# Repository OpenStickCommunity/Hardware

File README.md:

# Open Stick Community hardware repo

This repository is a collection of open-source hardware designs which have been submitted to the project.

# Designs

3D Prints

- [3D Printable Stand - Small](/3D%20Prints/3D%20Printable%20Stand/README.md) - Designed by TheTrain
- [3D Printable Stand - Large](/3D%20Prints/3D%20Printable%20Stand/README.md) - Designed by TheTrain
- [3D Printable Fightstick Case](/3D%20Prints/Fightstick%20Case/README.md) - Designed by TheTrain
- [3D Printable Open Stick Mini](/3D%20Prints/Open%20Stick%20Mini/README.md) - Designed by TheTrain
- [3D Printable Fightstick Case XL](/3D%20Prints/Fightstick%20Case/Community%20submissions/3D%20print%20files/Fightstick%20XL/Open%20Stick%20XL%20-%20Main%20Frame%20(x4%20Buttons).stl) - Designed by Lucipher
- [3D Printable Open Stick Modular](/3D%20Prints/Open%20Stick%20Modular%20(OSM)/README.md) - Designed by TheTrain
- [3D Printable Open Stick Modular - Mini](/3D%20Prints/Open%20Stick%20Modular%20-%20Mini%20(OSM-Mini)/README.md) - Designed by TheTrain
- [3D Printable Open Stick Modular - Slim](/3D%20Prints/Open%20Stick%20Modular%20-%20Slim%20(OSM-Slim)/README.md) - Designed by TheTrain
- [3D Printable Open Stick Astro](/3D%20Prints/Open%20Stick%20Astro%20(OSASTRO)/README.md) - Designed by TheTrain
- [3D Printable OSBMX v2 Buttons](/3D%20Prints/OSBMX%20v2/README.md) - Designed by TheTrain
- [3D Printable OSBLP v2 Buttons](/3D%20Prints/OSBLP%20v2/README.md) - Designed by TheTrain
- [3D Printable OSBMX v2 SiTong Edition Buttons](/3D%20Prints/OSBMX%20v2/Community%20submissions/OSBMX%20v2%20-%20SiTong%20Edition/README.md) - Designed by TheTrain (remixed from the OSBLP v2 by TheTrain)
- [3D Printable OSBLP v2 SiTong Edition Buttons](/3D%20Prints/OSBLP%20v2/Community%20submissions/OSBLP%20v2%20-%20SiTong%20Edition/README.md) - Designed by TheTrain (remixed from the OSBLP v2 by TheTrain)
- [3D Printable OSBHE v2 Buttons](/3D%20Prints/OSBHE%20v2/README.md) - Designed by TheTrain
- [3D Printable OSB Plug](/3D%20Prints/OSB%20Plug/README.md) - Designed by TheTrain
- [3D Printable OSB Analog Stick](/3D%20Prints/OSB%20Analog%20Stick/README.md) - Designed by TheTrain
- [Open Source Arcade Stand - OSAS](/3D%20Prints/Open%20Source%20Arcade%20Stand%20(OSAS)/README.md) - Designed by TheTrain

GP2040-CE Official Boards

- [RP2040 Advanced Breakout Board v5.6E with USB Passthrough](/Boards/GP2040-CE%20Official%20Boards/RP2040%20Advanced%20Breakout%20Board/RP2040%20Advanced%20Breakout%20Board%20-%20Passthrough/README.md) - Designed by TheTrain
- [RP2040 Advanced Breakout Board v5.2E (no USB Passthrough)](/Boards/GP2040-CE%20Official%20Boards/RP2040%20Advanced%20Breakout%20Board/RP2040%20Advanced%20Breakout%20Board/README.md) - Designed by TheTrain
- [RP2040 Basic Breakout Board v5.4E with USB Passthrough](/Boards/GP2040-CE%20Official%20Boards/RP2040%20Basic%20Breakout%20Board/RP2040%20Basic%20Breakout%20Board%20-%20Passthrough/README.md) - Designed by TheTrain
- [RP2040 Basic Breakout Board v5.4E (no USB Passthrough)](/Boards/GP2040-CE%20Official%20Boards/RP2040%20Basic%20Breakout%20Board/RP2040%20Basic%20Breakout%20Board/README.md) - Designed by TheTrain
- [RP2040 Mini Breakout Board v7.5E with USB Passthrough](/Boards/GP2040-CE%20Official%20Boards/RP2040%20Mini%20Breakout%20Board/RP2040%20Mini%20Breakout%20Board%20-%20Passthrough/README.md) - Designed by TheTrain
- [RP2040 Mini Breakout Board v7.3E (no USB Passthrough)](/Boards/GP2040-CE%20Official%20Boards/RP2040%20Mini%20Breakout%20Board/RP2040%20Mini%20Breakout%20Board/README.md) - Designed by TheTrain
- [RP2040 Quick Solder Breakout Board v1.0 (no USB Passthrough)](/Boards/GP2040-CE%20Official%20Boards/RP2040%20Quick%20Solder%20Breakout%20Board/README.md) - Designed by TheTrain

GP2040-CE Official Controllers

- [ARC Accessibility Controller](/Boards/GP2040-CE%20Official%20Controllers/ARC%20Accessibility%20Controller/README.md) - Designed by TheTrain
- [Flatbox Rev 5 RGB](/Boards/GP2040-CE%20Official%20Controllers/Flatbox%20Rev%205%20RGB/README.md) - Remixed by TheTrain from the Flatbox Rev 5 by Jfedor
- [Flatbox Rev 5 Passthrough](/Boards/GP2040-CE%20Official%20Controllers/Flatbox%20Rev%205%20Passthrough/README.md) - Remixed by TheTrain from the Flatbox Rev 5 by Jfedor
- [Open_Core0 v2.0](/Boards/GP2040-CE%20Official%20Controllers/Open_Core0/README.md) - Designed by TheTrain
- [Open_Core0 WASD v2.0](/Boards/GP2040-CE%20Official%20Controllers/Open_Core0%20WASD/README.md) - Designed by TheTrain
- [Open_Core0 MIXUP](/Boards/GP2040-CE%20Official%20Controllers/Open_Core0%20MIXUP/README.md) - Designed by TheTrain
- [Zero_Rhythm v1.0](/Boards/GP2040-CE%20Official%20Controllers/Zero%20Rhythm/README.md) - Designed by TheTrain
- [Pocket Pad](/Boards/GP2040-CE%20Official%20Controllers/Pocket%20Pad/README.md) - Designed by TheTrain
- [Pocket Pad WASD](/Boards/GP2040-CE%20Official%20Controllers/Pocket%20Pad%20WASD/README.md) - Designed by TheTrain
- [Mini Pad](/Boards/GP2040-CE%20Official%20Controllers/Mini%20Pad/README.md) - Designed by TheTrain

Retail Stick Replacement Boards

- [Hori Fighting Edge PS3 (FE PS3)](/Boards/Retail%20Stick%20Replacement%20Boards/Hori%20Fighting%20Edge%20PS3%20(FE%20PS3)/README.md) - Designed by TheTrain
- [Hori Fighting Edge PS4 (FE PS4)](/Boards/Retail%20Stick%20Replacement%20Boards/Hori%20Fighting%20Edge%20PS4%20(FE%20PS4)/README.md) - Designed by TheTrain
- [Hori Real Arcade Pro N PS4 (RAP N PS4)](/Boards/Retail%20Stick%20Replacement%20Boards/Hori%20Real%20Arcade%20Pro%20N%20PS4%20(RAP%20N%20PS4)/README.md) - Designed by TheTrain
- [Hori Real Arcade Pro VLX PS3 (RAP VLX PS3)](/Boards/Retail%20Stick%20Replacement%20Boards/Hori%20Real%20Arcade%20Pro%20VLX%20PS3%20(RAP%20VLX%20PS3)/README.md) - Designed by TheTrain
- [SEGA Dreamcast Twin Stick (with USB Passthrough)](/Boards/Retail%20Stick%20Replacement%20Boards/SEGA%20Dreamcast%20Twin%20Stick%20(with%20USB%20Passthrough)/README.md) - Designed by indigotrance

Supported Boards

- [Ghost Auth v2.0](/Boards/Supported%20Boards/Ghost%20Auth/README.md) - Designed by TheTrain
- [GP2040 Keyboard converter](/Boards/Supported%20Boards/GP2040%20Keyboard%20Converter/Waveshare%20Zero-PCB/README.md) - Designed by Infraredaces
- [USB Pasthrough Add-on Board](/Boards/Supported%20Boards/USB%20Passthrough%20Board/README.md) - Designed by TheTrain
- [Tiny USB Hub v1.2 - 2x USB with USB C](/Boards/Supported%20Boards/USB%20Hubs/Tiny%20USB%20Hub%20v1.2e/README.md) - Designed by TheTrain
- [Tiny USB Hub v1.3 - 2x USB Direct Connect](/Boards/Supported%20Boards/USB%20Hubs/Tiny%20USB%20Hub%20v1.3e/README.md) - Designed by TheTrain
- [Tiny USB Hub v1.3 v2 - 2x USB Direct Connect](/Boards/Supported%20Boards/USB%20Hubs/Tiny%20USB%20Hub%20v1.3e%20v2/README.md) - Designed by TheTrain
- [Tiny USB Hub v1.4 - 4x USB Direct Connect](/Boards/Supported%20Boards/USB%20Hubs/Tiny%20USB%20Hub%20v1.4e/README.md) - Designed by TheTrain
- [HE Breakout Board v1.1](/Boards/Supported%20Boards/HE%20Breakout%20Board/README.md) - Designed by TheTrain
- [RPBoy v1.0](/Boards/Supported%20Boards/RPBoy/README.md) - Designed by TheTrain
- [RPBoy Mini v2.0](/Boards/Supported%20Boards/RPBoy%20Mini/README.md) - Designed by TheTrain

Miscellaneous

- [Haute42/COSMOX Bottom Foam](/Miscellaneous/Haute42%20COSMOX%20Bottom%20Foam/README.md) - Designed by TheTrain
- [Sanjuks V3 AM5 Adapter Plate](/Miscellaneous/Sanjuks%20V3%20AM5%20Adapter%20Plate/README.md) - Designed by TheTrain
- [Sanjuks Style Nobi Topper](/Miscellaneous/Sanjuks%20Style%20Nobi%20Topper/README.md) - Designed by TheTrain
- [Open LED Project - Sanwa 30mm RGB LEDs](/Miscellaneous/Open%20LED%20Project%20-%20Sanwa%2030mm%20RGB%20LED/README.md) - Designed by TheTrain
- [Open LED Project - Addressable RGB LED Light Bar](/Miscellaneous/Open%20LED%20Project%20-%20Addressable%20RGB%20LED%20Light%20Bar/README.md) - Designed by TheTrain
- [Nintendo Switch Art Cart](/Miscellaneous/Nintendo%20Switch%20Art%20Carts/README.md) - Designed by TheTrain, art template by TheTrain
- [Sanwa JLF Plate Cover](/Miscellaneous/Sanwa%20JLF%20Plate%20Cover/README.md) - Designed by TheTrain

Trains Vewlix Stuff

- [Vewlix Coin Return Adapter](/Trains%20Vewlix%20Stuff/Vewlix%20Coin%20Return%20Adapter/README.md) - Designed by TheTrain
- [Vewlix Coin Return Slot](/Trains%20Vewlix%20Stuff/Vewlix%20Coin%20Return%20Slot/README.md) - Designed by TheTrain
- [Vewlix Coin Mech](/Trains%20Vewlix%20Stuff/Vewlix%20Coin%20Mech/README.md) - Designed by TheTrain
- [Vewlix Stickers](/Trains%20Vewlix%20Stuff/Vewlix%20Stickers/README.md) - Remixes and customs by TheTrain
- [Vewlix Control Panel SiTong Adapter Rings](/Trains%20Vewlix%20Stuff/Vewlix%20Control%20Panel%20SiTong%20Adapter%20Rings/README.md) - Designed by TheTrain
- [Vewlix NESiCA NFC Reader](/Trains%20Vewlix%20Stuff/Vewlix%20NESiCA%20NFC%20Reader/README.md) - Designed by TheTrain
- [Vewlix Sub-Panel Art and Cut Files](/Trains%20Vewlix%20Stuff/Vewlix%20Sub-Panel%20Art%20and%20Cut%20Files/README.md) - Designed by Jermaine Davis

Trains Sim Racing Stuff

- [Logitech G PRO RS Wheel Hub wall mount](/Trains%20Sim%20Racing%20Stuff/Logitech%20G%20PRO%20RS%20Wheel%20Hub%20wall%20mount/README.md) - Designed by TheTrain
- [Logitech G PRO RS Wheel Hub 4040 mount](/Trains%20Sim%20Racing%20Stuff/Logitech%20G%20PRO%20RS%20Wheel%20Hub%204040%20mount/README.md) - Designed by TheTrain
- [Logitech G PRO RS Wheel Hub Shifter Pad Mod](/Trains%20Sim%20Racing%20Stuff/Logitech%20RS%20Wheel%20Hub%20Shifter%20Pad%20Mod/README.md) - Designed by TheTrain
- [Logitech G PRO RS Wheel Rim template](/Trains%20Sim%20Racing%20Stuff/Logitech%20G%20PRO%20RS%20Wheel%20Rim%20template/README.md) - Designed by TheTrain
- [Wind Sim](/Trains%20Sim%20Racing%20Stuff/Wind%20Sim/README.md) - Designed by TheTrain
- [LapTimer](/Trains%20Sim%20Racing%20Stuff/Laptimer/README.md) - Designed by TheTrain
- [Porsche GT3 R Plate](/Trains%20Sim%20Racing%20Stuff/Porsche%20911%20GT3%20R%20plate/README.md) - Designed by TheTrain

Trains Theatrhythm Stuff
- [Theatrhythm - All-Star Carnival Manual](/Trains%20Theatrhythm%20Stuff/Theatrhythm%20Manual/Theatrhythm%20-%20All-Star%20Carnival%20-%20Manual.pdf)
- [Theatrhythm - All-Star Carnival JLF Shaft](/Trains%20Theatrhythm%20Stuff/Theatrhythm%20JLF%20shaft/README.md) - Designed by LayerShift
- [Theatrhythm - All-Star Carnival Side Plexi Art](/Trains%20Theatrhythm%20Stuff/Theatrhythm%20ASC%20Arcade%20Cabinet%20Art/Theatrhythm%20ASC%20Side%20Plexi%20Art/README.md) - Designed by TheTrain
- [Theatrhythm - All-Star Carnival Front Control Panel Art](/Trains%20Theatrhythm%20Stuff/Theatrhythm%20ASC%20Arcade%20Cabinet%20Art/Theatrhythm%20ASC%20Front%20Control%20Panel%20Art/README.md) - Designed by TheTrain
- [Theatrhythm - All-Star Carnival NESiCA Reader Art](/Trains%20Theatrhythm%20Stuff/Theatrhythm%20ASC%20Arcade%20Cabinet%20Art/Theatrhythm%20ASC%20NESiCA%20Reader%20Art/README.md) - Designed by TheTrain
- [Theatrhythm - All-Star Carnival Coin Sticker Art](/Trains%20Theatrhythm%20Stuff/Theatrhythm%20ASC%20Arcade%20Cabinet%20Art/Theatrhythm%20ASC%20Coin%20Sticker%20Art/README.md) - Designed by TheTrain

Trains Arcade Machine Manual Stuff

- [Taito Vewlix L - Manual - Part 1](/Trains%20Vewlix%20Stuff/Vewlix%20Manual/Taito%20Vewlix%20L%20-%20Manual%20-%20Part%201.pdf)
- [Taito Vewlix L - Manual - Part 2](/Trains%20Vewlix%20Stuff/Vewlix%20Manual/Taito%20Vewlix%20L%20-%20Manual%20-%20Part%202.pdf)
- [Taito Vewlix L - Manual - Part 3](/Trains%20Vewlix%20Stuff/Vewlix%20Manual/Taito%20Vewlix%20L%20-%20Manual%20-%20Part%203.pdf)
- [Theatrhythm - All-Star Carnival](/Trains%20Theatrhythm%20Stuff/Theatrhythm%20Manual/Theatrhythm%20-%20All-Star%20Carnival%20-%20Manual.pdf)

Tutorials

- [Focus Attack RGB LED Board Configuration](/Tutorials/Focus%20Attack%20LED%20Board%20Configuration/README.md) for the [RP2040 Advanced Breakout Board v5.6](/Boards/GP2040-CE%20Official%20Boards/RP2040%20Advanced%20Breakout%20Board/RP2040%20Advanced%20Breakout%20Board%20-%20Passthrough/README.md) - Written by TheTrain
- [USB Passthrough Add-on Board Installation](/Tutorials/USB%20Passthrough%20Board%20Installation/README.md) - Written by TheTrain
- [Logitech RS Wheel Hub Shifter Pad Mod](/Tutorials/Logitech%20RS%20Wheel%20Hub%20Shifter%20Pad%20Mod/README.md) - Written by TheTrain

Vendor Resources

- [GP2040-CE Logo Files](/Vendor%20Resources/GP2040-CE%20Logo%20files/README.md)

# Contributing

Any design submitted to this repository must be submitted by the original copyright holder and include a [license](#licensing). If your license requires attribution, you must provide details on how to appropriately attribute the design.

# Copyright

All copyrights are retained by the original author(s) unless the copyright is explicitly transferred to the Open Stick Community.

# Licensing

Check the LICENSE of each design for details on how the design can be used.

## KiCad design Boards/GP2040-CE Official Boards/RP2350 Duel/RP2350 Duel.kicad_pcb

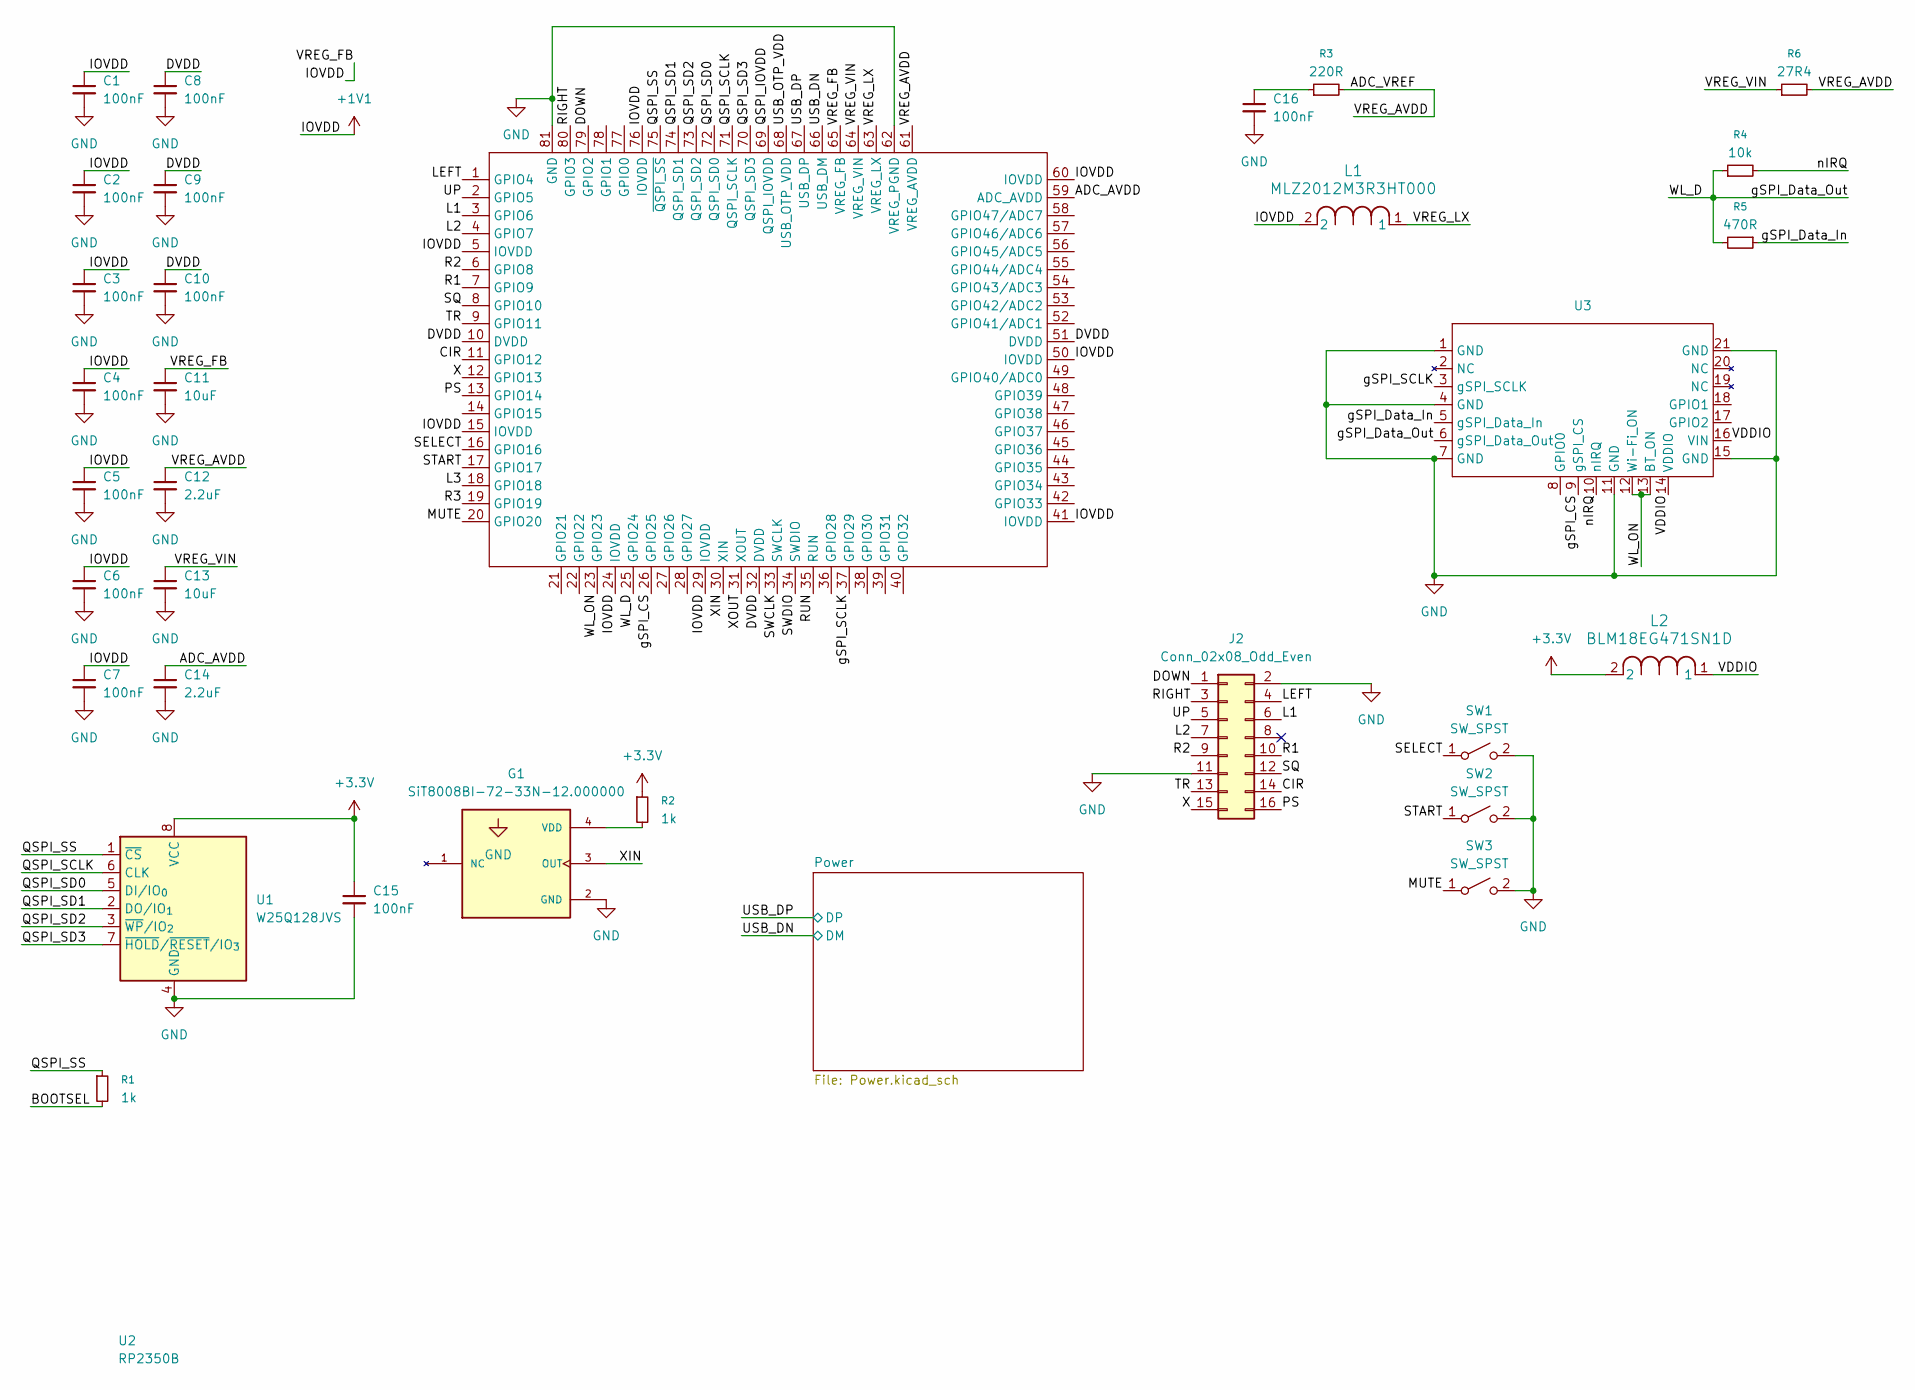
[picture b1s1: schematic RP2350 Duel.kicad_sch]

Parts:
C1, C2, C3, C4, C5, C6, C7, C8, C9, C10, C15, C16: 100nF; C_0603_1608Metric_Pad1.08x0.95mm_HandSolder
C11, C13: 10uF; C_0603_1608Metric_Pad1.08x0.95mm_HandSolder
C12, C14: 2.2uF; C_0603_1608Metric_Pad1.08x0.95mm_HandSolder
G1: SiT8008BI-72-33N-12.000000; OSC_SiT8008BI-72-33N-12.000000; PARTREV 1.08
J2: Conn_02x08_Odd_Even; FlexPCB
L1: MLZ2012M3R3HT000; IND_2012_TDK
L2: BLM18EG471SN1D; IND_BLM18_0603_MUR
R1, R2: 1k; R_0603_1608Metric_Pad0.98x0.95mm_HandSolder
R3: 220R; R_0603_1608Metric_Pad0.98x0.95mm_HandSolder
R4: 10k; R_0603_1608Metric_Pad0.98x0.95mm_HandSolder
R5: 470R; R_0603_1608Metric_Pad0.98x0.95mm_HandSolder
R6: 27R4; R_0603_1608Metric_Pad0.98x0.95mm_HandSolder
SW1, SW2, SW3: SW_SPST; SKRWAEE030
U1: W25Q128JVS; SOIC-8_5.3x5.3mm_P1.27mm
U2: RP2350B; QFN-80-1EP_10x10mm_P0.4mm_EP3.4x3.4mm
U3: RM2

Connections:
+1V1: C1.1, C2.1, C3.1, C4.1, C5.1, C6.1, C7.1, C11.1, L1.2, U2.5 (IOVDD), U2.15 (IOVDD), U2.24 (IOVDD), U2.29 (IOVDD), U2.41 (IOVDD), U2.50 (IOVDD), U2.60 (IOVDD), U2.65 (VREG_FB), U2.76 (IOVDD)
+3.3V: C15.1, L2.2, R2.1, U1.8 (VCC); also elsewhere on the board
/ADC_AVDD: C14.1, U2.59 (ADC_AVDD)
/ADC_VREF: C12.1, R3.2, R6.2, U2.61 (VREG_AVDD)
/BOOTSEL: R1.2
/CIR: J2.14, U2.11 (GPIO12)
/DOWN: J2.1, U2.79 (GPIO2)
/DVDD: C8.1, C9.1, C10.1, U2.10 (DVDD), U2.32 (DVDD), U2.51 (DVDD)
/L1: J2.6, U2.3 (GPIO6)
/L2: J2.7, U2.4 (GPIO7)
/L3: U2.18 (GPIO18)
/LEFT: J2.4, U2.1 (GPIO4)
/MUTE: SW3.1 (A), U2.20 (GPIO20)
/PS: J2.16, U2.13 (GPIO14)
/QSPI_IOVDD: U2.69 (QSPI_IOVDD)
/QSPI_SCLK: U1.6 (CLK), U2.71 (QSPI_SCLK)
/QSPI_SD0: U1.5 (DI/IO_{0}), U2.72 (QSPI_SD0)
/QSPI_SD1: U1.2 (DO/IO_{1}), U2.74 (QSPI_SD1)
/QSPI_SD2: U1.3 (~WP/IO_{2}), U2.73 (QSPI_SD2)
/QSPI_SD3: U1.7 (~HOLD/~RESET/IO_{3}), U2.70 (QSPI_SD3)
/QSPI_SS: R1.1, U1.1 (~CS), U2.75 (~QSPI_SS)
/R1: J2.10, U2.7 (GPIO9)
/R2: J2.9, U2.6 (GPIO8)
/R3: U2.19 (GPIO19)
/RIGHT: J2.3, U2.80 (GPIO3)
/RUN: U2.35 (RUN)
/SELECT: SW1.1 (A), U2.16 (GPIO16)
/SQ: J2.12, U2.8 (GPIO10)
/START: SW2.1 (A), U2.17 (GPIO17)
/SWCLK: U2.33 (SWCLK)
/SWDIO: U2.34 (SWDIO)
/TR: J2.13, U2.9 (GPIO11)
/UP: J2.5, U2.2 (GPIO5)
/USB_DN: U2.66 (USB_DM); also elsewhere on the board
/USB_DP: U2.67 (USB_DP); also elsewhere on the board
/USB_OTP_VDD: U2.68 (USB_OTP_VDD)
/VDDIO: L2.1, U3.14 (VDDIO), U3.16 (VIN)
/VREG_LX: L1.1, U2.63 (VREG_LX)
/VREG_VIN: C13.1, R6.1, U2.64 (VREG_VIN)
/WL_D: R4.1, R5.2, U2.25 (GPIO24), U3.6 (gSPI_Data_Out)
/WL_ON: U2.23 (GPIO23), U3.12 (Wi-Fi_ON), U3.13 (BT_ON)
/X: J2.15, U2.12 (GPIO13)
/XIN: G1.3 (OUT), U2.30 (XIN)
/XOUT: U2.31 (XOUT)
/gSPI_CS: U2.26 (GPIO25), U3.9 (gSPI_CS)
/gSPI_Data_In: R5.1, U3.5 (gSPI_Data_In)
/gSPI_SCLK: U2.37 (GPIO29), U3.3 (gSPI_SCLK)
/nIRQ: R4.2, U3.10 (nIRQ)
GND: C1.2, C2.2, C3.2, C4.2, C5.2, C6.2, C7.2, C8.2, C9.2, C10.2, C11.2, C12.2, C13.2, C14.2, C15.2, C16.2, G1.2 (GND), J2.2, J2.11, SW1.2 (B), SW2.2 (B), SW3.2 (B), U1.4 (GND), U2.62 (VREG_PGND), U2.81 (GND), U3.1 (GND), U3.4 (GND), U3.7 (GND), U3.11 (GND), U3.15 (GND), U3.21 (GND); also elsewhere on the board
unnamed: C16.1, R3.1
unnamed: G1.4 (VDD), R2.2

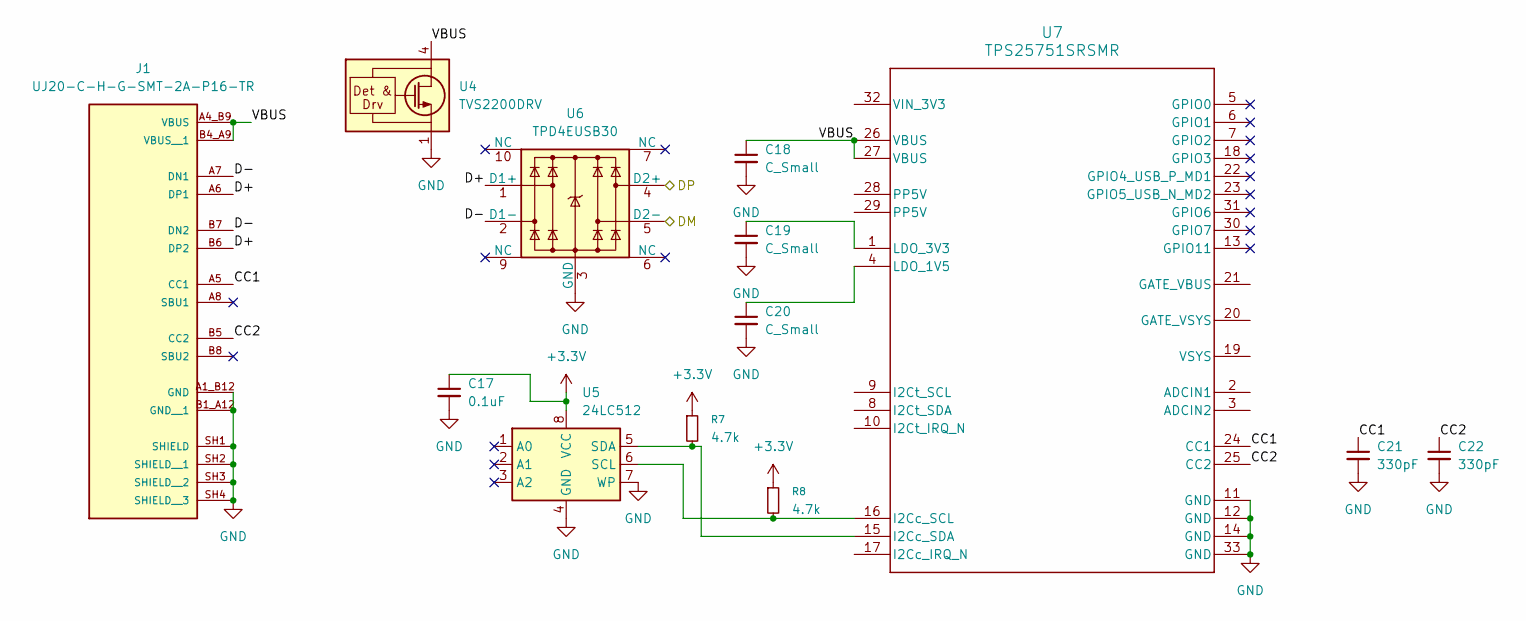
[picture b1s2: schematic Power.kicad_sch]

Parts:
C17: 0.1uF; C_0603_1608Metric_Pad1.08x0.95mm_HandSolder
C18, C19, C20: C_Small; C_0603_1608Metric_Pad1.08x0.95mm_HandSolder
C21, C22: 330pF; C_0603_1608Metric_Pad1.08x0.95mm_HandSolder
J1: UJ20-C-H-G-SMT-2A-P16-TR; SAMESKY_UJ20-C-H-G-SMT-2A-P16-TR; PARTREV 1.0
R7, R8: 4.7k; R_0603_1608Metric_Pad0.98x0.95mm_HandSolder
U4: TVS2200DRV; WSON-6-1EP_2x2mm_P0.65mm_EP1x1.6mm
U5: 24LC512
U6: TPD4EUSB30; USON-10_2.5x1.0mm_P0.5mm
U7: TPS25751SRSMR; RSM0032B-MFG

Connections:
+3.3V: C17.1, R7.1, R8.1, U5.8 (VCC); also elsewhere on the board
/Power/CC1: C21.1, J1.A5 (CC1), U7.24 (CC1)
/Power/CC2: C22.1, J1.B5 (CC2), U7.25 (CC2)
/Power/D+: J1.A6 (DP1), J1.B6 (DP2), U6.1 (D1+)
/Power/D-: J1.A7 (DN1), J1.B7 (DN2), U6.2 (D1-)
/Power/VBUS: C18.1, J1.A4_B9 (VBUS), J1.B4_A9 (VBUS__1), U4.4 (IN), U4.5 (IN), U4.6 (IN), U7.26 (VBUS), U7.27 (VBUS)
/USB_DN: U6.5 (D2-); also elsewhere on the board
/USB_DP: U6.4 (D2+); also elsewhere on the board
GND: C17.2, C18.2, C19.2, C20.2, C21.2, C22.2, J1.A1_B12 (GND), J1.B1_A12 (GND__1), J1.SH1 (SHIELD), J1.SH2 (SHIELD__1), J1.SH3 (SHIELD__2), J1.SH4 (SHIELD__3), U4.1 (GND), U4.2 (GND), U4.3 (GND), U4.7 (GND), U5.4 (GND), U5.7 (WP), U6.3 (GND), U6.8 (GND), U7.11 (GND), U7.12 (GND), U7.14 (GND), U7.33 (GND); also elsewhere on the board
unnamed: R8.2, U5.6 (SCL), U7.16 (I2Cc_SCL)
unnamed: R7.2, U5.5 (SDA), U7.15 (I2Cc_SDA)
unnamed: C20.1, U7.4 (LDO_1V5)
unnamed: C19.1, U7.1 (LDO_3V3)

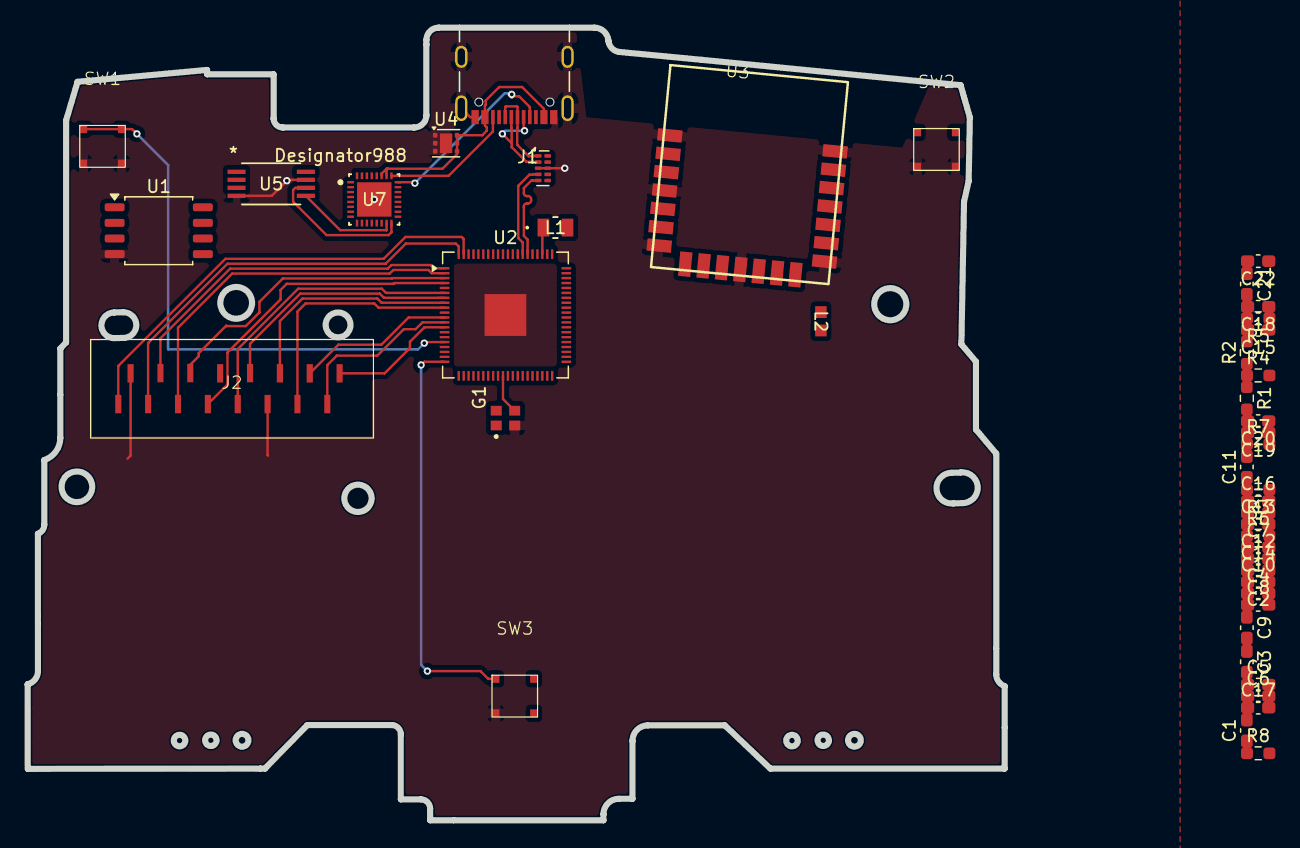
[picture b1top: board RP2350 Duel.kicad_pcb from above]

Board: 4 copper layers, 79.5 x 64.5 mm, 45 parts (0 on the bottom side), 51 nets.

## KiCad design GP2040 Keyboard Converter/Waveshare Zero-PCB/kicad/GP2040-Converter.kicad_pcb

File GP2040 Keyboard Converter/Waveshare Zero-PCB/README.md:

# GP2040-CE Keyboard Converter

---

***NOTE: Keyboard Host Configuration has not yet been implemented into the GP2040-CE project as part of the Main Release as of GP2040-CE v0.7.3***

## Attribution

The following text must be included in any distribution of derivitives of this board. All links must also be included.

Copyright 2023 [InfraredAces](https://github.com/InfraredAces)

[Licensed under CC BY 4.0](https://creativecommons.org/licenses/by/4.0/)

Changes from the original design:
  - list any changes you make here

## Summary

The GP2040-CE Keyboard Converter Case is designed to be a USB Host Device for the use of a keyboard with the GP2040-CE project. The end result is a device that allows you to play on a keyboard, but have it registered just as GP2040-CE controller, whether that is XInput, DInput, PS4, or Switch.

You can find a pre-compiled .UF2 firmware file for the RP2040 Advanced Breakout Board in the GP2040-CE release section under `GP2040-CE_X.X.X_WaveshareZero-KeyboardConverter.uf2`.

We have a small but passionate Discord group which you can access here if interested: https://discord.com/invite/k2pxhke7q8

A massive thank you to [FeralAI](https://github.com/FeralAI) who made most of this possible!

## Assembly

### Circuit Board

These circuit boards are designed to be ordered through a PCB fabricator and components soldered on by the end user.    

Once the circuit boards have been fabricated and received the following parts are necessary for assembly.

| Solder Order | Component Name | Quantity Required Per Board | Link to Example Component |
| :----------: | :------------- | --------------------------: | :-----------------------: |
| 1 | Waveshare Zero (**without headers**) | 1 | [Waveshare - Waveshare Zero](https://www.waveshare.com/product/rp2040-zero.html) |
| 2 | USB A THT Port | 1 | [DigiKey - USB-A-S-RA-SMT](https://www.digikey.com/en/products/detail/adam-tech/USB-A-S-RA-SMT/9832349) |
| 3 | 6x6x13.5mm THT Tactile Switch | 6 | [DigiKey - TL1105KF160Q](https://www.digikey.com/en/products/detail/e-switch/TL1105KF160Q/1805437) | 

Note: THT: Through Hole Technology Mounting 

It's recommended that the Waveshare Zero be flashed first with the most recent version of GP2040-CE and then test the boards for proper functioning before soldering to the primary board.

Please note that we are not responsible for issues that arrise from the manufactuing of these boards done any manufacturer.  These board files have been ordered and tested for functionality.  

### 3D Printed Case

| Hardware Name | Quantity Required Per Board | Link to Example Hardware |
| :------------: | --------------------------: | :-----------------------: |
| M2x18mm Screws | 4 | [McMaster-Carr](https://www.mcmaster.com/92000A024/) |
| M2x1.6mm Nuts | 4 | [McMaster-Carr](https://www.mcmaster.com/90592A075/) |

The screws are inserted through the top and pass though the PCB and out the bottom. The nuts can be embedded in the recesses on the bottom of the case. An alternative is to use glue to hole them permanently in place.

## How to upload firmware

### Uploading the firmware before assembly

Hold the BootSel button on the Waveshare Zero and plug the device into your computer.  It will show up as an external device.  Copy the `GP2040-CE_X.X.X_WaveshareZero-KeyboardConverter.uf2` file to it and wait for the device to disconnect after copying completes.  

### Uploading the firmware after assembly

Plug the GP2040-CE Keyboard Converter into your computer and quickly press the BootSel button twice on the GP2040-CE Keyboard Converter.  You should see an external device show up on your computer.  Copy the `GP2040-CE_X.X.X_WaveshareZero-KeyboardConverter.uf2` file to it and wait for the device to disconnect after copying completes.  

### Flashing for Troubleshooting
If something goes wrong and you want to upload the firmware again (or if you have tested out the configuration tool and made a mistake) you can enter BootSel mode via either of the methods above and drag over the included `flash_nuke.uf2` file.  This file will take a moment to write to the Pico, once completed you will see the device disconnect and then re-connect as an external device.  After it has shown up again you can copy the same `GP2040-CE_X.X.X_WaveshareZero-KeyboardConverter.uf2` firmware over to it again.

## Sales recommendations

Through the licensing, you are free to make and sell these boards in group buys or even commercial applications.  

The intended purpose of this board, as well as the overall GP2040-CE project is to get low cost boards into the hands of as many people as possible to everyone can enjoy the project.  

As such, we have a recommend MSRP of $20 USD for the GP2040-CE Keyboard Converter or $30 USD with free shipping within the USA or Canada.

You are free to set your own price as you see fit. 
## Acknowledgements

- [FeralAI](https://github.com/FeralAI) for starting the GP2040 project and the original design of the Pico Fighting Board
- Everyone that works on the GP2040-CE project to make it the best controller firmware around

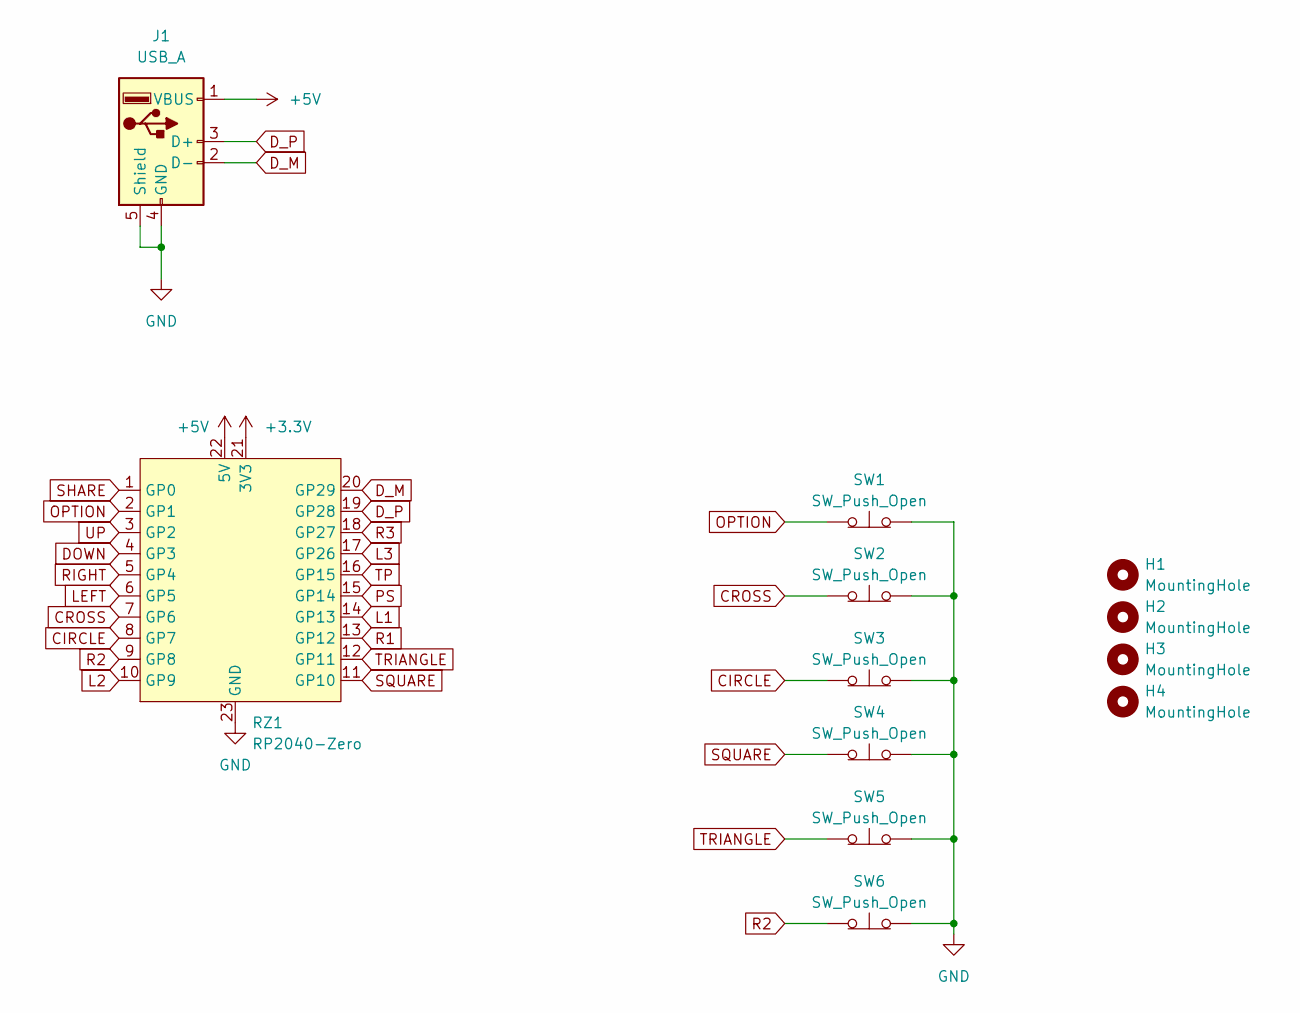
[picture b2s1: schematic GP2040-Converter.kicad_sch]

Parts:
H1, H2, H3, H4: MountingHole; MountingHole_2.2mm_M2
J1: USB_A; USB_A_TE_292303-7_Horizontal; LCSC C2763378
RZ1: RP2040-Zero
SW1, SW2, SW3, SW4, SW5, SW6: SW_Push_Open; SW_PUSH_6mm_H13mm; LCSC C278322

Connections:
+3.3V: RZ1.21 (3V3)
+5V: J1.1 (VBUS), RZ1.22 (5V)
CIRCLE: RZ1.8 (GP7), SW3.1 (A)
CROSS: RZ1.7 (GP6), SW2.1 (A)
DOWN: RZ1.4 (GP3)
D_M: J1.2 (D-), RZ1.20 (GP29)
D_P: J1.3 (D+), RZ1.19 (GP28)
GND: J1.4 (GND), J1.5 (Shield), RZ1.23 (GND), SW1.2 (B), SW2.2 (B), SW3.2 (B), SW4.2 (B), SW5.2 (B), SW6.2 (B)
L1: RZ1.14 (GP13)
L2: RZ1.10 (GP9)
L3: RZ1.17 (GP26)
LEFT: RZ1.6 (GP5)
OPTION: RZ1.2 (GP1), SW1.1 (A)
PS: RZ1.15 (GP14)
R1: RZ1.13 (GP12)
R2: RZ1.9 (GP8), SW6.1 (A)
R3: RZ1.18 (GP27)
RIGHT: RZ1.5 (GP4)
SHARE: RZ1.1 (GP0)
SQUARE: RZ1.11 (GP10), SW4.1 (A)
TP: RZ1.16 (GP15)
TRIANGLE: RZ1.12 (GP11), SW5.1 (A)
UP: RZ1.3 (GP2)

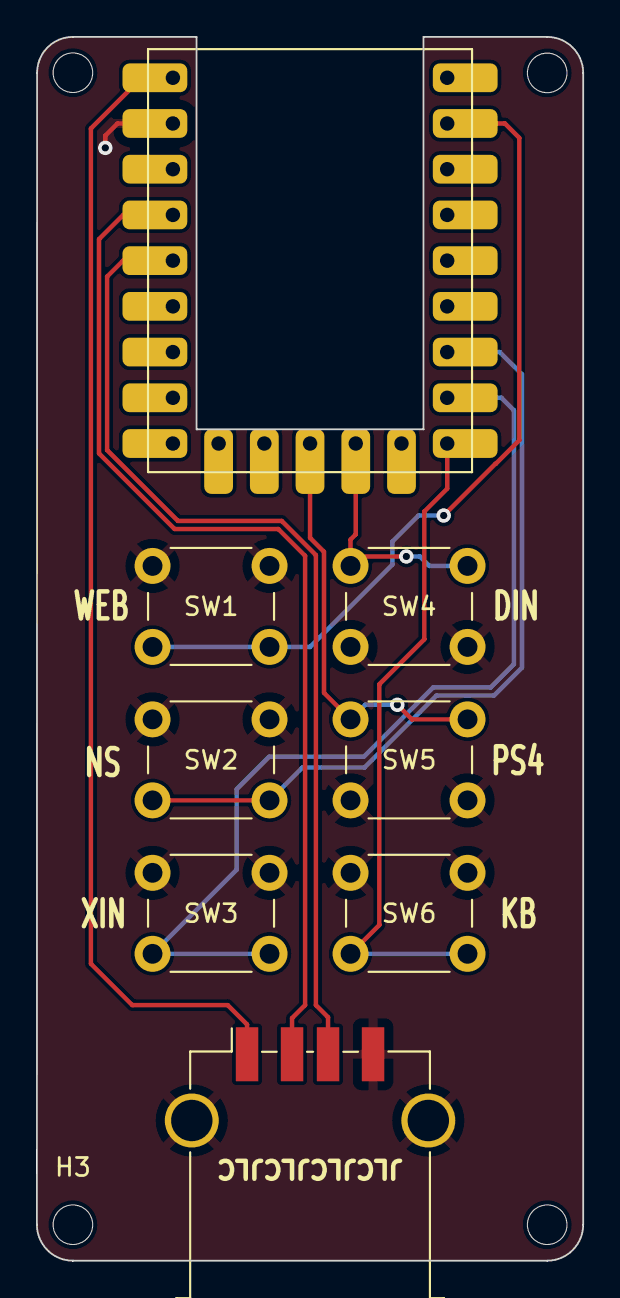
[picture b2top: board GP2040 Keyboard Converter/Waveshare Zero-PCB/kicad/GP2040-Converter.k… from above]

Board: 2 copper layers, 30.4 x 68.0 mm, 12 parts (0 on the bottom side), 10 nets.

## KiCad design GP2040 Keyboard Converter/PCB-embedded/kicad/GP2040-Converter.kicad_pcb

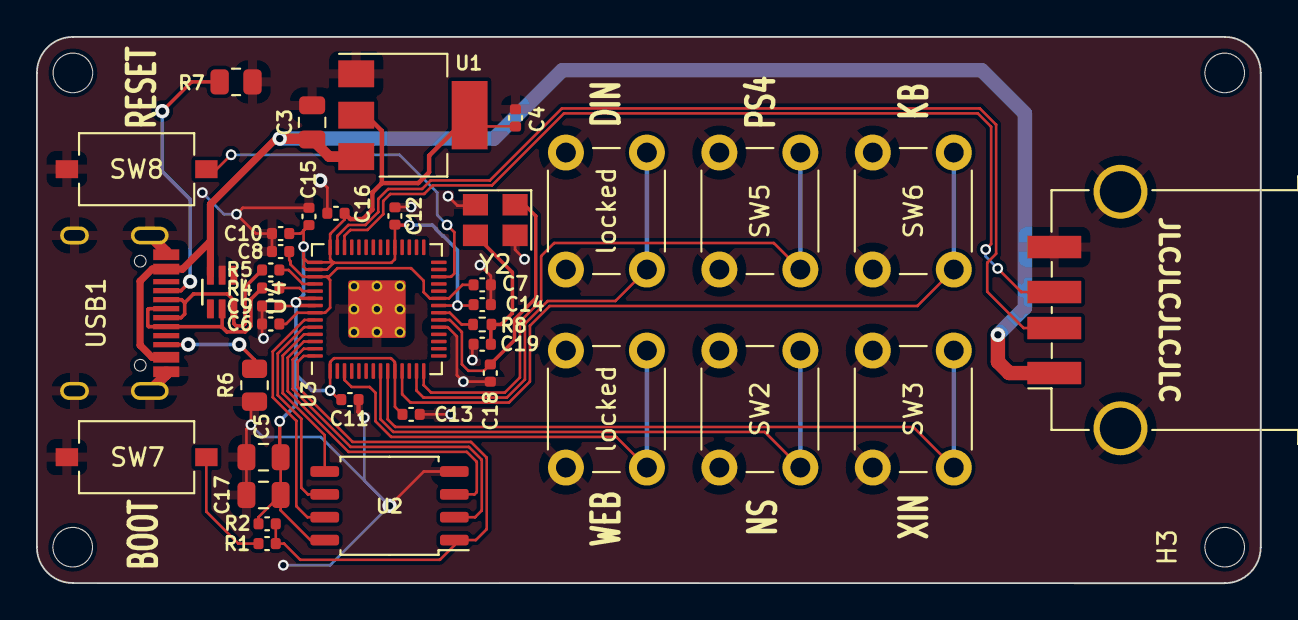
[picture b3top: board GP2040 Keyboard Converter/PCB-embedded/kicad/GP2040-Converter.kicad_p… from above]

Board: 2 copper layers, 68.0 x 30.4 mm, 43 parts (0 on the bottom side), 29 nets.

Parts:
C3, C5, C17: 10u; C_0805_2012Metric
C4, C6, C7, C9, C11, C12, C13, C14, C15, C16: 100n; C_0402_1005Metric
C8, C10: 1u; C_0402_1005Metric
C18, C19: 30p; C_0402_1005Metric
H1, H2, H3, H4: MountingHole; MountingHole_2.2mm_M2
J1: USB_A; USB_A_TE_292303-7_Horizontal
R1: 1k; C_0402_1005Metric
R2: 10k; C_0402_1005Metric
R4, R5: 27; C_0402_1005Metric
R6, R7: 5.1k; R_0805_2012Metric
R8: 1k; R_0402_1005Metric
SW2, SW3, SW5, SW6: SW_Push_Open; SW_PUSH_6mm_H13mm
SW7, SW8: SW_Push_Open; SW_Tactile_SPST_NO_Straight_CK_PTS636Sx25SMTRLFS
U1: NCP1117-3.3_SOT223; SOT-223-3_TabPin2
U2: W25Q128JVS; SOIC-8_5.23x5.23mm_P1.27mm
U3: RP2040; RP2040-QFN-56
U4: SMF05CT1G; SOT65P210X110-6N
USB1: HRO-TYPE-C-31-M-12; HRO-TYPE-C-31-M-12-Assembly
Y2: Crystal_GND24; Crystal_SMD_3225-4Pin_3.2x2.5mm
locked: locked; SW_PUSH_6mm_H13mm
locked#2: SW_Push_Open; SW_PUSH_6mm_H13mm

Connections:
+1V1: C6.1, C7.1, C8.1, U3.23 (DVDD), U3.45 (VREG_VOUT), U3.50 (DVDD)
+3V3: C4.1, C5.1, C9.1, C10.1, C11.1, C12.1, C13.1, C14.1, C15.1, C16.1, C17.1, R2.1, U1.2 (VO), U2.8 (VCC), U3.1 (IOVDD), U3.10 (IOVDD), U3.22 (IOVDD), U3.33 (IOVDD), U3.42 (IOVDD), U3.43 (ADC_AVDD), U3.44 (VREG_IN), U3.48 (USB_VDD), U3.49 (IOVDD)
+5V: C3.1, J1.1 (VBUS), U1.3 (VI), U4.3, USB1.2 (VBUS), USB1.11 (VBUS)
/QSPI_SCLK: U2.6 (CLK), U3.52 (QSPI_SCLK)
/QSPI_SD0: U2.5 (DI(IO0)), U3.53 (QSPI_SD0)
/QSPI_SD1: U2.2 (DO(IO1)), U3.55 (QSPI_SD1)
/QSPI_SD2: U2.3 (IO2), U3.54 (QSPI_SD2)
/QSPI_SD3: U2.7 (IO3), U3.51 (QSPI_SD3)
/QSPI_SS: R1.1, R2.2, U2.1 (~CS), U3.56 (QSPI_SS)
/RUN: SW8.2 (B), U3.26 (RUN)
/USB_D+: R4.1, U4.5, USB1.6 (DP1), USB1.8 (DP2)
/USB_D-: R5.1, U4.6, USB1.5 (DN2), USB1.7 (DN1)
/XIN: C18.2, U3.20 (XIN), Y2.1
/XOUT: R8.2, U3.21 (XOUT)
/~USB_BOOT: R1.2, SW7.2 (B)
CIRCLE: SW3.1 (A), U3.9 (GPIO7)
CROSS: SW2.1 (A), U3.8 (GPIO6)
D_M: J1.2 (D-), U3.41 (GPIO29_ADC3)
D_P: J1.3 (D+), U3.40 (GPIO28_ADC2)
GND: C3.2, C4.2, C5.2, C6.2, C7.2, C8.2, C9.2, C10.2, C11.2, C12.2, C13.2, C14.2, C15.2, C16.2, C17.2, C18.1, C19.2, J1.4 (GND), J1.5 (Shield), R6.2, R7.2, SW2.2 (B), SW3.2 (B), SW5.2 (B), SW6.2 (B), SW7.1 (A), SW8.1 (A), U1.1 (GND), U2.4 (GND), U3.19 (TESTEN), U3.57 (GND), U4.2, USB1.1 (GND), USB1.12 (GND), USB1.13 (SHIELD), Y2.2, Y2.4, locked.2 (B), locked#2.2 (B)
unnamed: C19.1, R8.1, Y2.3
unnamed: R5.2, U3.46 (USB_DM)
unnamed: R4.2, U3.47 (USB_DP)
unnamed: R7.1, USB1.4 (CC1)
unnamed: R6.1, USB1.10 (CC2)
OPTION: U3.3 (GPIO1), locked#2.1 (A)
R2: SW6.1 (A), U3.11 (GPIO8)
SQUARE: U3.13 (GPIO10), locked.1 (A)
TRIANGLE: SW5.1 (A), U3.14 (GPIO11)

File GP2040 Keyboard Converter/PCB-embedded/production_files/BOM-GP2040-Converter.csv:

Comment,Designator,Footprint,LCSC
10u,"C17,C19,C3,C5",C_0805_2012Metric,C1046
10k,R2,C_0402_1005Metric,C11616
1k,"R1,R8",C_0402_1005Metric,C11702
100n,"C11,C12,C13,C14,C15,C16,C4,C6,C7,C9",C_0402_1005Metric,C1525
30p,C18,C_0402_1005Metric,C1570
SMF05CT1G,U4,SOT65P210X110-6N,C15879
HRO-TYPE-C-31-M-12,USB1,HRO-TYPE-C-31-M-12-Assembly,C165948
NCP1117-3.3_SOT223,U1,SOT-223-3_TabPin2,C185806
RP2040,U3,RP2040-QFN-56,C2040
27,"R4,R5",C_0402_1005Metric,C25100
5.1k,"R6,R7",R_0805_2012Metric,C27834
SW_Push_Open,"SW7,SW8",SW_Tactile_SPST_NO_Straight_CK_PTS636Sx25SMTRLFS,C329185
USB_A,J1,USB_A_TE_292303-7_Horizontal,C42641
1u,"C10,C8",C_0402_1005Metric,C52923
SW_Push_Open,"SW1,SW2,SW3,SW4,SW5,SW6",SW_PUSH_6mm_H13mm,C557902
Crystal_GND24,Y2,Crystal_SMD_3225-4Pin_3.2x2.5mm,C9002
W25Q128JVS,U2,SOIC-8_5.23x5.23mm_P1.27mm,C97521
MountingHole,H4,MountingHole_2.2mm_M2,
MountingHole,H1,MountingHole_2.2mm_M2,
MountingHole,H3,MountingHole_2.2mm_M2,
MountingHole,H2,MountingHole_2.2mm_M2,

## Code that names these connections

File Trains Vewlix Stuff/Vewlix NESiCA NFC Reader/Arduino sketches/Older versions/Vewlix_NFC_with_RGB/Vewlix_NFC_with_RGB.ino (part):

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constexpr int down_pin = 2;  // DOWN   | DOWN   | DOWN    | DOWN     | DOWN   | DOWN   |
constexpr int left_pin = 3;  // LEFT   | LEFT   | LEFT    | LEFT     | LEFT   | LEFT   |
constexpr int right_pin = 6; // RIGHT  | RIGHT  | RIGHT   | RIGHT    | RIGHT  | RIGHT  |
constexpr int p1_pin = 7;    // B3     | X      | Y       | Square   | 1      | P1     |
constexpr int p2_pin = 8;    // B4     | Y      | X       | Triangle | 4      | P2     |
constexpr int p3_pin = 9;    // R1     | RB     | R       | R1       | 6      | P3     |
constexpr int p4_pin = 10;   // L1     | LB     | L       | L1       | 5      | P4     |
constexpr int k1_pin = 11;   // B1     | A      | B       | Cross    | 2      | K1     |
constexpr int k2_pin = 12;   // B2     | B      | A       | Circle   | 3      | K2     |
constexpr int k3_pin = 13;   // R2     | RT     | ZR      | R2       | 8      | K3     |
constexpr int k4_pin = 14;   // L2     | LT     | ZL      | L2       | 7      | K4     |
constexpr int s1_pin = 15;   // S1     | Back   | Minus   | Select   | 9      | Coin   |
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
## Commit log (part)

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2023-09-17 Update to v2.0 (#49)
2023-09-20 Open_Core0
2023-09-20 Open_Core0 (#50)
2023-09-21 Spelling pass for Keyboard Converter
2023-09-21 spelling pass for ghost auth
2023-09-21 spell pass on open_core0
2023-09-21 spell pass on open stick case
2023-09-21 Comprehensive fix of errors in documentation. (#20)
    * minor typo fix on readme
    * Fix for typos, minor spelling mistakes, instances of weird grammar in Flatbox Rev 5 RGB readme.
    about 5 instances of typos on the word "design", I imagine it's particulary hard on the wrist. an instance where "done" is used instead of "does" among numerous other fixesx
    * Update README.md
    * Spelling fix on Flatbox Premium Art Case
    * further fixes on main rev 5 rgb readme
2023-09-21 Community submission section
2023-09-21 Community submission section (#51)
2023-09-21 20230921 fightstick case community section (#52)
    * Community submission section
    * update
2023-09-23 v5.4E - PT
2023-09-23 v5.4E - PT (#53)
2023-09-24 Adds pre-compiled UF2 for the ABB
2023-09-24 Create test
2023-09-24 Create test (#55)
2023-09-24 Firmware upload
2023-09-25 Remix Submission: updating SnugNeutrikReadMe
2023-09-25 Changing ReadMe name
2023-09-28 Update README.md
    Typo in MSRP
2023-09-28 Update README.md (#56)
    Typo in MSRP
2023-10-02 Update - Open_Core0 WASD
    All files for the Open_Core0 WASD
2023-10-02 Update - Open_Core0 WASD (#57)
    All files for the Open_Core0 WASD
2023-10-08 Update with logo files
2023-10-08 Update with logo files (#59)
2023-10-11 Adding new variations of Neutrik Hole and updating ReadMe (#46)
    * Increasing depth of Neutrik hole from 2 to 3.54mm
    * Updating README / Reverting step / adding new ver
    * Remix Submission: updating SnugNeutrikReadMe
    * Changing ReadMe name
2023-10-22 Delete Open_Core0/PRERELEASE FIRMWARE directory
    This is being removed because there is full firmware in the main repo now.
2023-10-22 Update README.md
    Updating the firmware section since there is a proper release now.
2023-11-06 Update
    Updated Gerber removing my logo and adding the generic GP2040-CE logo as well as the Open Source logo
2023-11-06 Add files via upload
    Updated Gerber removing my logo and adding the generic GP2040-CE logo as well as the Open Source logo
2023-11-06 Add files via upload
    Updated PCB files by removing my logo and adding the generic GP2040-CE logo as well as the Open Source logo
2023-11-06 Add files via upload
    Updated PCB by removing my logo and adding the generic GP2040-CE logo as well as the Open Source logo
2023-11-18 Update README.md
    Updating for the `H3,H4 designators don't exist in the BOM file.` change with JLC
2023-11-22 Add the Sanjuks V3 AM5 adapter plate
2023-11-22 Update README.md
    Edited for spelling, formatting, and clarity
2023-11-22 Update README.md (#62)
    Edited for spelling, formatting, and clarity
2023-11-23 Update for v6 boards
2023-11-23 Update for v6 boards (#63)
    * Update for v6 boards
    * Update README.md
2023-11-26 3D printable stand
2023-11-26 3D printable stand (#64)
    * 3D printable stand
    * Update README.md
2023-11-29 Add large stand
2023-11-29 Add large stand (#65)
2023-12-19 RP2040 Basic Breakout
2024-01-25 Update
    Added stab bar back into Open_Core0 WASD
2024-01-28 Update for v5.5 (#66)
2024-03-17 Update GP2040 info card - Passthrough v5.5.pdf
    While looking through this vendor resource I noticed that the GPIO pin descriptions on the third page of this PDF have GPIO 20, 21, and 22 mixed up. Across the affected JST 4-pin and screw terminal b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
2024-03-28 Fightstick XL addition to the community submissions!
2024-04-01 Added Shoikenstar based on AFS layout
2024-04-12 v5.6
2024-04-12 v5.6 (#71)
2024-04-12 Fightstick XL addition to the community submissions! (#70)
    * Fightstick XL addition to the community submissions!
    * Added Shoikenstar based on AFS layout
2024-04-18 Add art template files for Flatbox Rev 5 RGB case
2024-04-23 Update with .STEP for ABB v5.6
    This PR adds the .STEP file for the RP2040 Advanced Breakout Board - Version 5.6 - PT
2024-04-24 Experimental mouse switch button PCBs
    This is an experimental PCB for mouse switch buttons. This has not yet been tested and there is no houseing or cap for them
2024-04-24 Experimental mouse switch button PCBs (#72)
    This is an experimental PCB for mouse switch buttons. This has not yet been tested and there is no houseing or cap for them
2024-04-24 Update hardware repo with vendor resources for LED install
2024-04-24 Update hardware repo with vendor resources for LED install (#73)
2024-04-26 Re-org of the hardware repo
    This is expected to break all links.
2024-04-26 Update to structure
2024-04-27 Add RP2040 Mini Breakout Board with USB Passthrough
2024-04-27 Add Hori FE PS4
2024-04-27 Hori RAP N PS4
2024-04-27 Hori FE PS3
2024-04-27 Update photos
2024-04-28 Update to foam files
2024-04-28 Update to main readme
2024-04-28 Changed hyperlinks to be on the names rather than "HERE"
    Suggested by jfedor on discord
2024-04-28 Changed hyperlinks to be on the names rather than "HERE" (#75)
    Suggested by jfedor on discord
2024-04-30 Update pics
2024-05-01 Updated with coloring sheet
2024-05-05 Update with vendor info for larger orders
2024-05-05 Update with vendor info for larger orders (#76)
2024-05-05 Update to board repo layout
2024-05-05 Update to board repo layout (#78)
2024-05-05 Updates to image links and folder names
2024-05-05 20240505 cleanup (#79)
    * Update to board repo layout
    * Updates to image links and folder names
2024-05-05 Updates to links
2024-05-05 20240505 cleanup (#80)
    * Update to board repo layout
    * Updates to image links and folder names
    * Updates to links
2024-05-05 20240505 cleanup (#81)
    * Update to board repo layout
    * Updates to image links and folder names
    * Updates to links
    * Update
2024-05-05 Update links
2024-05-05 20240505 cleanup (#82)
    * Update to board repo layout
    * Updates to image links and folder names
    * Updates to links
    * Update
    * Update links
2024-05-05 20240505 cleanup (#83)
    * Update to board repo layout
    * Updates to image links and folder names
    * Updates to links
    * Update
    * Update links
    * Update
2024-05-15 Adds Zero_Rhythm
2024-05-17 ARC controller
2024-05-17 ARC base module
2024-05-30 Removed invalid ':' character so Windows will still work with Hardware folder
2024-06-03 Update - Foam cuts for Haute42
    Updated foam cuts for:
    - T-12 Clear
    - T-16 Clear
    - R16
2024-06-09 Add OSM-Mini
    Adds files for the OSM-Mini
2024-06-15 Add Flatbox Rev5 Passthrough (#85)
2024-06-15 OSM (#87)
2024-06-22 Top plate blank template
2024-07-28 Update - Add TMNT case
2024-07-31 Changes to ReadMe.MD files
    Five Readme files have been updated. The nature of all Readme updates is the same. For each of the following files, all the images referenced in the beginning lines of the Readme have had their filep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
    1. 3D printable Stand ReadMe
    2. Fightstick Case ReadMe
    3. Fightstick Case Community Submissions ReadMe
    4. Ghost Auth ReadMe
    5. USB Passthrough Board ReadMe
2024-07-31 Revert changes to RABB v5.5 info card
    RABB v5.5 info card copied from Main to eliminate any differences between file versions from previous commits.
2024-07-31 Updated Select Readme.MD files to fix broken images (#91)
    * Update GP2040 info card - Passthrough v5.5.pdf
    While looking through this vendor resource I noticed that the GPIO pin descriptions on the third page of this PDF have GPIO 20, 21, and 22 mixed up. Across the affected JST 4-pin and screw terminal b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
    * Changes to ReadMe.MD files
    Five Readme files have been updated. The nature of all Readme updates is the same. For each of the following files, all the images referenced in the beginning lines of the Readm
2024-08-03 Create Sega 2P 8x30mm
    I'm requesting to add the files I modified to make a Sega 2P layout for the OSM-Mini. It uses 8x 30mm buttons and a repositioned Neutrik passthrough cutout.
2024-08-13 Top plate blank template (#88)
2024-09-02 Add Sanjuks Style Nobi Topper
    Add Sanjuks Style Nobi Topper
2024-09-03 Add Vewlix Coin Return Button adapter
2024-09-04 Add coin mech
2024-09-04 Add coin mech (#93)
2024-09-04 20240903 vewlix coin insert (#94)
    * Add coin mech
    * Update README.md
2024-09-05 Update - NESiCA
2024-09-06 Coin return slot
2024-09-07 Vewlix SiTong Sapcers
2024-09-08 LED board - Sanwa
2024-09-08 Vewlix 100y sticker
2024-09-08 Fix for path and filename on sticker images
2024-09-11 Update - add Vewlix NFC reader
2024-10-30 Add Pocket Pad
2024-11-01 Pocket Pad WASD
2024-11-03 Mini Pad
2024-11-04 Update README.md (#95)
2024-12-04 Add RP2040 Quick Solder board
2024-12-09 RS racing stuff
2024-12-23 Added box switch osbmx plunger
2024-12-23 Added box switch osbmx plunger (#96)
2025-01-26 Logitech RS Hub shifter mod
2025-01-26 Logitech RS Hub shifter mod (#97)
2025-01-26 20250126 logitech hub shifter pads (#98)
    * Logitech RS Hub shifter mod
    * Update README.md
    * Update README.md
2025-01-26 Uppade
2025-01-26 Update (#100)
2025-01-26 20250126 logitech update (#101)
    * Update
    * Update README.md
2025-01-26 20250126 logitech update (#102)
    * Update
    * Update README.md
    * Update README.md
    * Update
2025-02-21 RGB LED light bar
2025-02-23 OSBMX v2
2025-02-23 OSBMX v2 (#103)
2025-02-26 Wind Sim
2025-02-26 Update to sim stuff + add Wind Sim Arduino code
2025-02-28 RS Rim template
2025-03-07 OSM-Slim
2025-03-24 Add Forza Laptimer
2025-03-25 Update - Add board for OSBMX v2
2025-03-27 R16 StreetFighter art
2025-04-04 Update OSM mounting size
2025-04-04 Update OSM mounting size (#105)
2025-04-10 OSBLP v2
2025-04-21 Tiny USB Hub + Vewlix Sub Panels
2025-04-25 Update - OSB Plug
2025-05-01 Adds OSB Analog Stick
2025-05-01 Fix various typos
2025-05-01 Fix typo
2025-05-04 Open_Core0 MIXUP
2025-05-10 Update ground
2025-05-18 OSASTRO
2025-05-23 Update with new hub designs
2025-05-24 SiTong edition
2025-05-26 Add OSBMX SiTong edition
2025-06-12 Update to add v1.3 v2
2025-06-25 Added some arcade manuals
2025-06-30 Updated NESiCA reader - version 2.0
2025-07-08 Open Stick Mini
2025-07-08 Open Stick Mini (#107)
2025-07-19 Porsche GT3 R Plate
2025-08-17 Add Nintendo Switch Art Cart
2025-08-23 update readme for typo
    Found a typo; decided to fix. Thanks for the write up!
2025-09-18 update readme for typo (#110)
    Found a typo; decided to fix. Thanks for the write up!
2025-09-18 Fix typos (#106)
    * Fix various typos
    * Fix typo
2025-09-26 Theatrhythm JLF shaft
2025-10-07 added files for SEGA Dreamcast Twin Stick drop-in replacement board
2025-10-07 Moved README file to correct location
2025-10-07 Fixed brackets in README
2025-10-10 Sanwa JLF Plate Cover
2025-10-12 Added photograph of Dreamcast twin stick PCB
2025-10-12 Added Dreamcast twin stick PCB listing to main README
2025-10-12 Implemented photograph to Dreamcast twin stick README
2025-10-12 DC TS readme amendment
2025-10-12 Added DC TS 3D files
2025-10-12 Restructured DC TS 3D files
2025-10-28 Add HE buttons + mux board
2025-11-04 Update - Theatrhythm ASC side plexi art
2025-11-07 Update - Coin Sticker
2025-11-10 Added STEP and CPL files.
2025-11-15 SEGA Dreamcast Twin Stick PCB files (#112)
    * added files for SEGA Dreamcast Twin Stick drop-in replacement board
    * Moved README file to correct location
    * Fixed brackets in README
    * Added photograph of Dreamcast twin stick PCB
    * Added Dreamcast twin stick PCB listing to main README
    * Implemented photograph to Dreamcast twin stick README
2025-11-15 Added the correct JSON source file.
2025-11-16 Removed incorrect JSON file.
2025-12-15 Fix spelling and renamed files
2025-12-15 Fix spelling and renamed files (#115)
2026-04-04 Add OSAS
2026-04-04 Spelling
2026-04-06 RPBoy

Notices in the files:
Trains Vewlix Stuff/Vewlix NESiCA NFC Reader/Arduino sketches/Older versions/Vewlix_NFC_with_RGB/Vewlix_NFC_with_RGB.ino:
Copyright 2024 [TheTrain](https://x.com/TheTrain24)(https://github.com/OpenStickCommunity)
